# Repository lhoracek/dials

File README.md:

# dials
Android Motorcycle Gauges app

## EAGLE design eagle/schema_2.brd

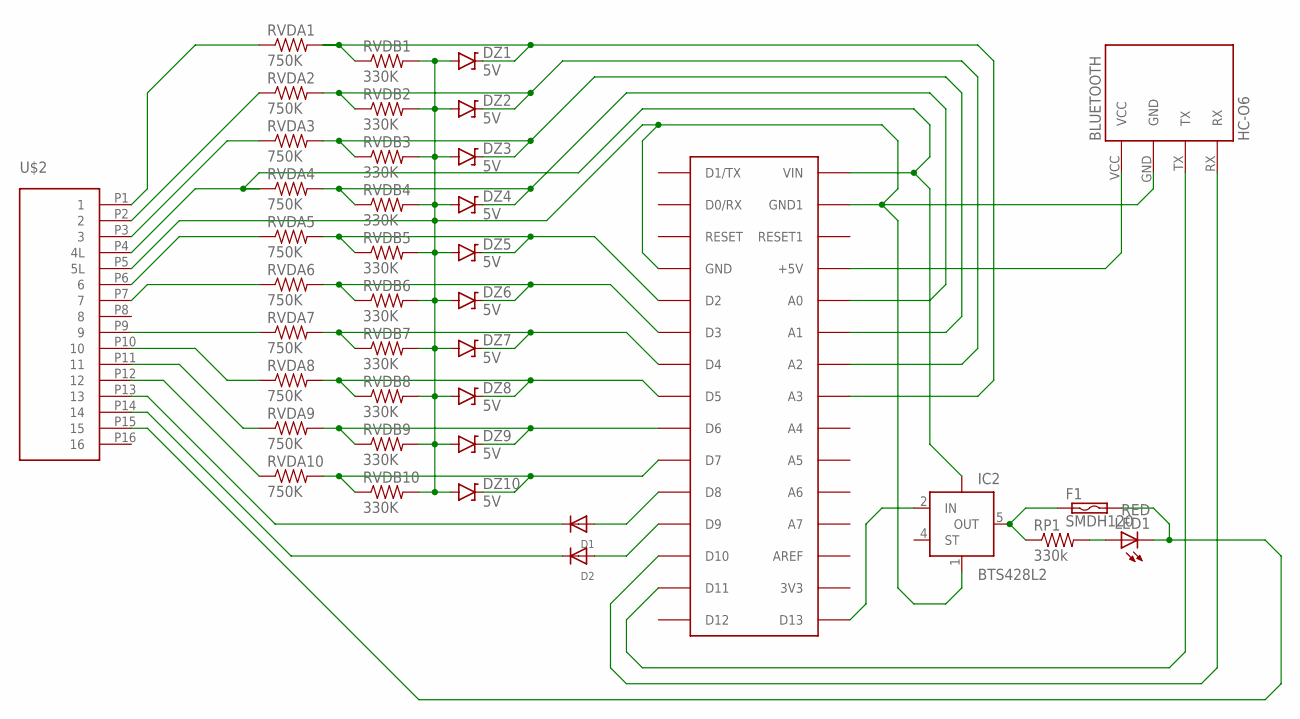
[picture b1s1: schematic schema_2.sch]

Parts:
BLUETOOTH: HC-O6; BT_BOARD_FOOTPRINT_STANDING
D1, D2: DIODESOD-123; SOD-123
DZ1, DZ2, DZ3, DZ4, DZ5, DZ6, DZ7, DZ8, DZ9, DZ10: 5V; SOD-123
F1: SMDH120; SMD050F
IC2: BTS428L2; TO252-5-11
LED1: RED; LED-1206
RP1: 330k; R2010
RVDA1, RVDA2, RVDA3, RVDA4, RVDA5, RVDA6, RVDA7, RVDA8, RVDA9, RVDA10: 750K; R2010
RVDB1, RVDB2, RVDB3, RVDB4, RVDB5, RVDB6, RVDB7, RVDB8, RVDB9, RVDB10: 330K; R2010
U$1: NANO; PDIP-32; MPN A000005
U$2: OBDII_SIDEMOUNTSIDEMOUNT; OBDII_SIDE

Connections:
GND: BLUETOOTH.GND, DZ1.A, DZ2.A, DZ3.A, DZ4.A, DZ5.A, DZ6.A, DZ7.A, DZ8.A, DZ9.A, DZ10.A, IC2.1 (GND), RVDB1.2, RVDB2.2, RVDB3.2, RVDB4.2, RVDB5.2, RVDB6.2, RVDB7.2, RVDB8.2, RVDB9.2, RVDB10.2, U$1.GND, U$1.GND1, U$2.P5 (5L)
unnamed: IC2.TAB (VBB), RVDA4.1, U$1.VIN, U$2.P4 (4L)
unnamed: RVDA1.1, U$2.P1 (1)
unnamed: BLUETOOTH.TX, U$1.D11
unnamed: BLUETOOTH.RX, U$1.D10
unnamed: RVDA2.1, U$2.P2 (2)
unnamed: RVDA3.1, U$2.P3 (3)
unnamed: DZ5.C, RVDA5.2, RVDB5.1, U$1.D2
unnamed: DZ6.C, RVDA6.2, RVDB6.1, U$1.D3
unnamed: DZ7.C, RVDA7.2, RVDB7.1, U$1.D4
unnamed: DZ8.C, RVDA8.2, RVDB8.1, U$1.D5
unnamed: DZ2.C, RVDA2.2, RVDB2.1, U$1.A2
unnamed: DZ3.C, RVDA3.2, RVDB3.1, U$1.A1
unnamed: DZ4.C, RVDA4.2, RVDB4.1, U$1.A0
unnamed: BLUETOOTH.VCC, U$1.+5V
unnamed: LED1.A, RP1.2
unnamed: IC2.2 (IN), U$1.D13
unnamed: F1.1, IC2.5 (OUT), RP1.1
unnamed: F1.2, LED1.C, U$2.P15 (15)
unnamed: DZ9.C, RVDA9.2, RVDB9.1, U$1.D6
unnamed: DZ10.C, RVDA10.2, RVDB10.1, U$1.D7
unnamed: D1.A, U$1.D8
unnamed: D2.A, U$1.D9
unnamed: RVDA5.1, U$2.P6 (6)
unnamed: RVDA6.1, U$2.P7 (7)
unnamed: RVDA7.1, U$2.P9 (9)
unnamed: RVDA8.1, U$2.P10 (10)
unnamed: RVDA9.1, U$2.P11 (11)
unnamed: RVDA10.1, U$2.P12 (12)
unnamed: D2.C, U$2.P14 (14)
unnamed: D1.C, U$2.P13 (13)
unnamed: DZ1.C, RVDA1.2, RVDB1.1, U$1.A3

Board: 2 copper layers, 39 parts (18 on the bottom side), 32 nets, no tracks yet.

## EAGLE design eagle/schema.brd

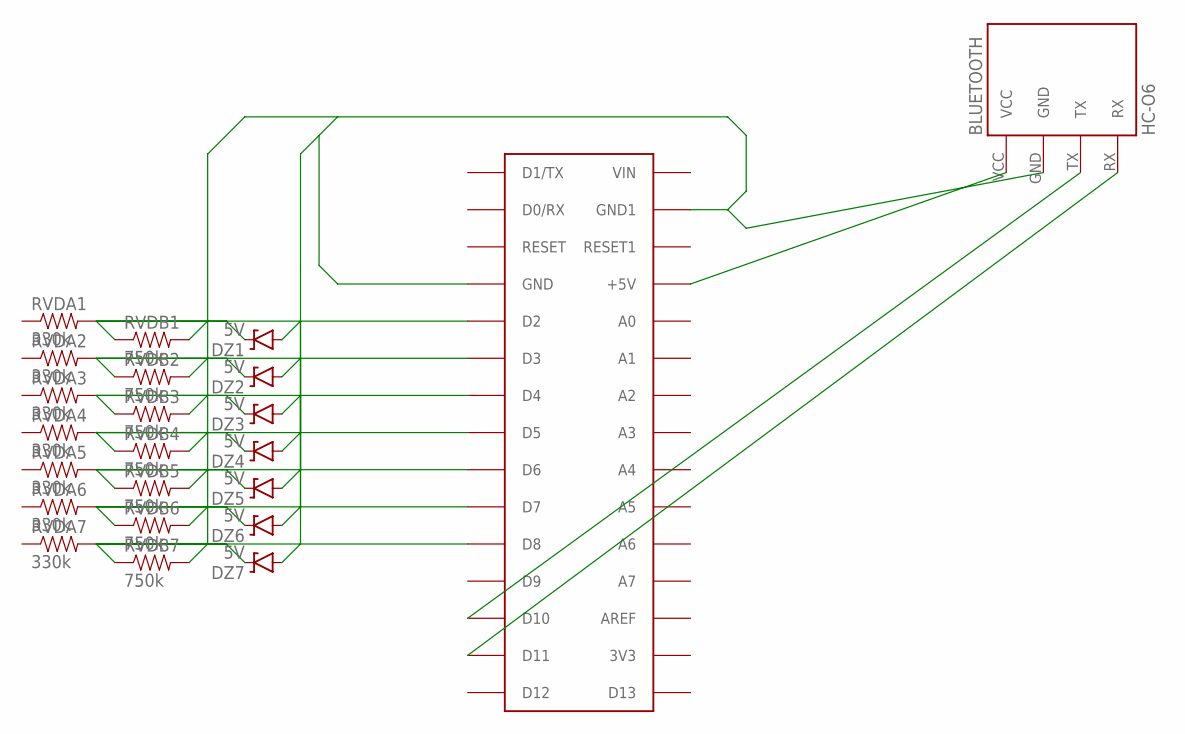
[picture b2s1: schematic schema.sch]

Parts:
BLUETOOTH: HC-O6; BT_BOARD_FOOTPRINT_STANDING
DZ1, DZ2, DZ3, DZ4, DZ5, DZ6, DZ7: 5V; SOD-123
RVDA1, RVDA2, RVDA3, RVDA4, RVDA5, RVDA6, RVDA7: 330k; R2010
RVDB1, RVDB2, RVDB3, RVDB4, RVDB5, RVDB6, RVDB7: 750k; R2010
U$1: NANO; PDIP-32; MPN A000005

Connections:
ARDUINO: BLUETOOTH.GND, DZ1.A, DZ2.A, DZ3.A, DZ4.A, DZ5.A, DZ6.A, DZ7.A, RVDB1.2, RVDB2.2, RVDB3.2, RVDB4.2, RVDB5.2, RVDB6.2, RVDB7.2, U$1.GND, U$1.GND1
unnamed: BLUETOOTH.VCC, U$1.+5V
unnamed: DZ1.C, RVDA1.2, RVDB1.1, U$1.D2
unnamed: BLUETOOTH.TX, U$1.D10
unnamed: BLUETOOTH.RX, U$1.D11
unnamed: DZ2.C, RVDA2.2, RVDB2.1, U$1.D3
unnamed: DZ3.C, RVDA3.2, RVDB3.1, U$1.D4
unnamed: DZ4.C, RVDA4.2, RVDB4.1, U$1.D5
unnamed: DZ5.C, RVDA5.2, RVDB5.1, U$1.D6
unnamed: DZ6.C, RVDA6.2, RVDB6.1, U$1.D7
unnamed: DZ7.C, RVDA7.2, RVDB7.1, U$1.D8

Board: 2 copper layers, 23 parts (0 on the bottom side), 11 nets, no tracks yet.

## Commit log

2016-01-25 init
2016-01-25 Arc view base
2016-01-25 Fullscreen activity
2016-01-25 New colors
2016-01-25 Basic layout
2016-01-25 Full layout
2016-01-26 RPM view nad layout enhancements
2016-01-26 Minor fixes
2016-01-26 Cleanup
2016-01-26 Test values
2016-01-26 Dynamic tests
2016-01-26 Icon
2016-01-26 RPM Scale, full dynamic test
2016-01-26 Removed RPM view and larger
2016-01-26 Coloring
2016-01-27 Off number labels
2016-02-09 Adding drawer
2016-02-10 Using Service
2016-11-19 Dependencies update
2016-11-19 Observable view model
2016-11-19 Immersive activity
2016-11-19 Databinding in layout
2016-11-19 Receiving bluetooth, fixed custom view memory issues
2016-11-19 Updated view binding
2016-11-19 Fix immersive on resume
2016-11-19 RST proof service
2016-11-19 AutoValue state definition
2016-11-19 Complete value set transmit
2016-11-20 Comms both ways
2016-11-21 Value smoothing
2016-11-21 New font an alignment
2016-11-21 Dial view aspect ratio
2016-11-22 Warning in small views
2016-11-22 Splash activity and zeroing in arduino
2016-11-22 SplashScreen
2016-11-22 Dials splash timer and immersive mode
2016-11-22 Notifications
2016-11-24 Splash screen for android 22 - bitmap
2016-11-24 Bluetooth state listener
2016-11-24 Event fired on BT state change
2016-11-24 Charging receiver with events
2016-11-25 Simple events for state changes
2016-11-25 Boot service start
2016-12-05 Service refactoring
2016-12-28 Eagle files
2016-12-28 Layout change
2017-10-28 Compilation fix
2017-10-28 Type adapter factory
2017-10-28 Splash and theme update
2017-10-28 Normalize colors
2017-10-31 UartService for BTLE
2018-05-06 fix scale
2019-01-02 refactoring comments
2019-01-03 Decoupled service and mock service
2019-01-03 Updated layout
2019-01-03 Update dependencies
2019-01-03 Updates to mock and maniactivity
2019-01-04 Updates to mocks
2019-01-04 Updated mocks
2019-01-04 gear display update
2019-01-04 Updates to dependencies, fix dialView
2019-01-05 Somewhat working bluetooth with rxjava 2
2019-01-05 Bluetooth working
2019-01-06 Bluetooth subscription cleanup
2019-01-06 Update service bluetooth disabling
2019-01-07 Controller
2019-01-07 New layout and frequency measuring
2019-01-07 Computing values

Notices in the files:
parts and their libraries:
SparkFun-Resistors: Licensing: Creative Commons ShareAlike 4.0 International - https://creativecommons.org/licenses/by-sa/4.0
